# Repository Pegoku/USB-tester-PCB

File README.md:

# USB-tester-PCB

This is a simple usb cable tester.

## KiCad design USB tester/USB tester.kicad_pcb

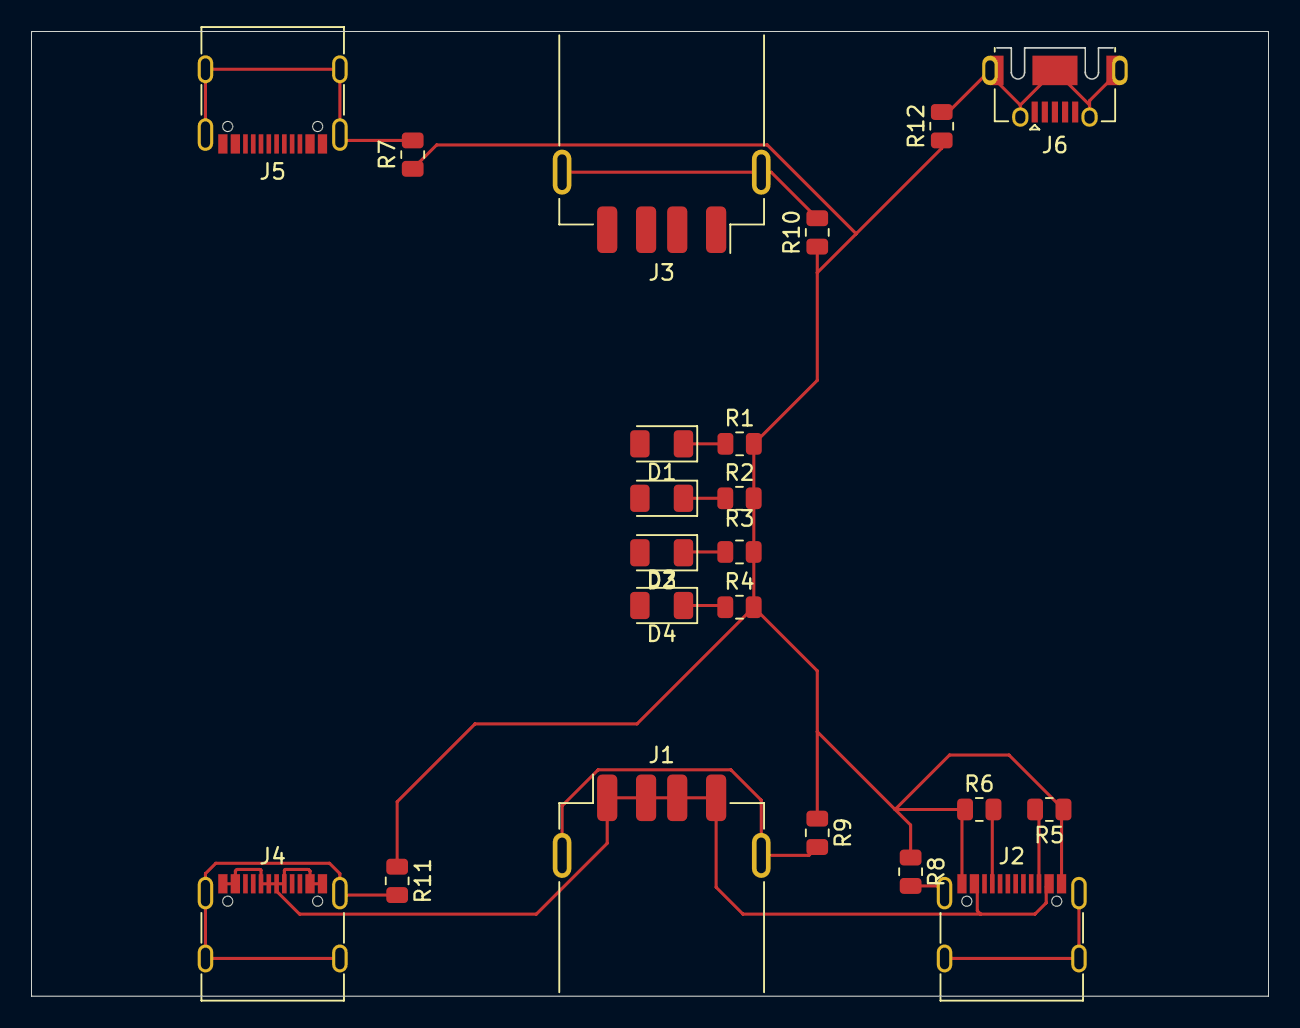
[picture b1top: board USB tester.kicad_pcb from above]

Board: 2 copper layers, 79.5 x 62.0 mm, 22 parts (0 on the bottom side), 18 nets.

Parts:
D1, D2, D3, D4: LED; LED_1206_3216Metric
J1, J3: USB_A; USB_A_Receptacle_GCT_USB1046
J2, J4, J5: USB_C_Receptacle_USB2.0_16P; USB_C_Receptacle_G-Switch_GT-USB-7010ASV
J6: USB_B_Micro; USB_Micro-AB_Molex_47590-0001
R1, R2, R3, R4: 13000; R_0805_2012Metric
R5, R6: 5.11k; R_0805_2012Metric
R7, R8, R9, R10, R11, R12: 1M; R_0805_2012Metric

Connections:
+5V: J1.1 (VBUS), J1.2 (D-), J1.3 (D+), J1.4 (GND), J2.A4 (VBUS), J2.A9 (VBUS), J2.B4 (VBUS), J2.B9 (VBUS), J4.A1 (GND), J4.A4 (VBUS), J4.A6 (D+), J4.A7 (D-), J4.A9 (VBUS), J4.A12 (GND), J4.B1 (GND), J4.B4 (VBUS), J4.B6 (D+), J4.B7 (D-), J4.B9 (VBUS), J4.B12 (GND)
GND: J2.A1 (GND), J2.A12 (GND), J2.B1 (GND), J2.B12 (GND), R1.2, R2.2, R3.2, R4.2, R5.1, R6.1, R7.1, R8.1, R9.1, R10.1, R11.1, R12.1
unnamed: D1.2 (A), J3.1 (VBUS), J5.A4 (VBUS), J5.A9 (VBUS), J5.B4 (VBUS), J5.B9 (VBUS), J6.1 (VBUS)
unnamed: D1.1 (K), R1.1
unnamed: D2.2 (A), J3.3 (D+), J5.A6 (D+), J5.B6 (D+), J6.3 (D+)
unnamed: D2.1 (K), R2.1
unnamed: D3.2 (A), J3.2 (D-), J5.A7 (D-), J5.B7 (D-), J6.2 (D-)
unnamed: D3.1 (K), R3.1
unnamed: D4.2 (A), J3.4 (GND), J5.A1 (GND), J5.A12 (GND), J5.B1 (GND), J5.B12 (GND), J6.5 (GND)
unnamed: D4.1 (K), R4.1
unnamed: J1.5 (Shield), R9.2
unnamed: J2.A5 (CC1), R6.2
unnamed: J2.B5 (CC2), R5.2
unnamed: J2.S1 (SHIELD), R8.2
unnamed: J3.5 (Shield), R10.2
unnamed: J4.S1 (SHIELD), R11.2
unnamed: J5.S1 (SHIELD), R7.2
unnamed: J6.6 (Shield), R12.2

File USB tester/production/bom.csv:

Designator,Footprint,Quantity,Value,LCSC Part #
"D1, D2, D3, D4",1206,4,LED,
"J1, J3",USB_A_Receptacle_GCT_USB1046,2,USB_A,
"J2, J4, J5",USB_C_Receptacle_G-Switch_GT-USB-7010ASV,3,USB_C_Receptacle_USB2.0_16P,
J6,USB_Micro-AB_Molex_47590-0001,1,USB_B_Micro,
"R1, R2, R3, R4",0805,4,13000,
"R10, R11, R12, R7, R8, R9",0805,6,1M,
"R5, R6",0805,2,5.11k,

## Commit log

2024-08-07 start
2024-08-07 finish
